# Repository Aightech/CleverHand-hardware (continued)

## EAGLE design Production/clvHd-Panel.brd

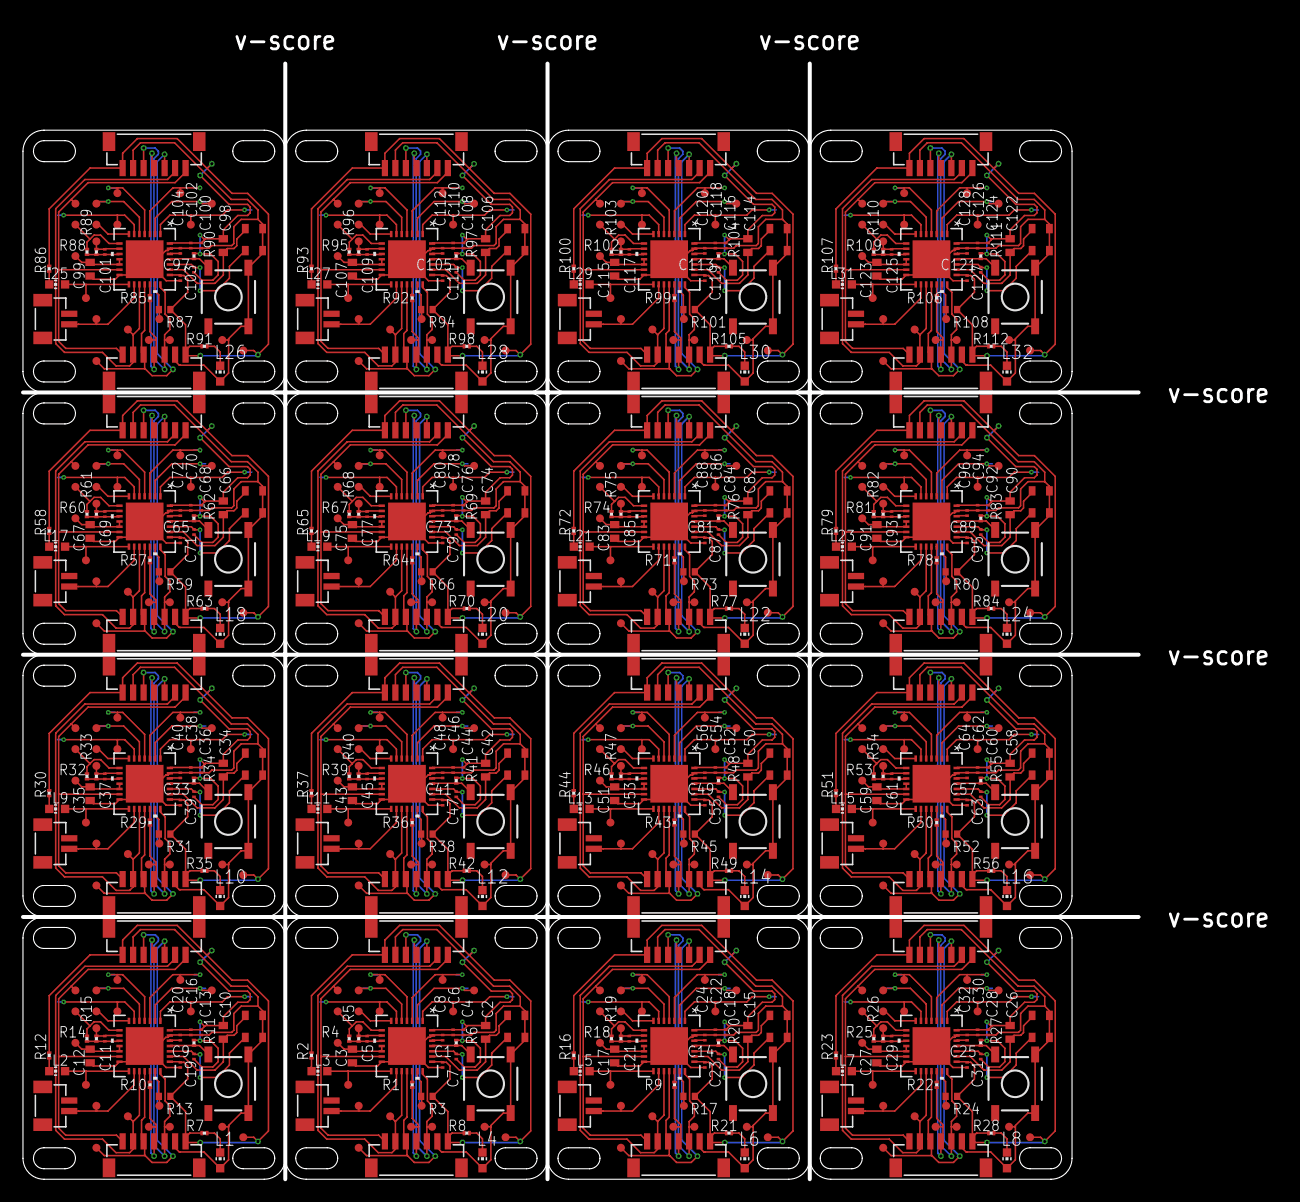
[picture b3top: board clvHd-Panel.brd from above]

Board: 2 copper layers, 106.3 x 106.3 mm, 688 parts (0 on the bottom side), 448 nets.

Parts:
C1, C9, C14, C25, C33, C41, C49, C57, C65, C73, C81, C89, C97, C105, C113, C121: 22pF; C0201
C2, C10, C15, C26, C34, C42, C50, C58, C66, C74, C82, C90, C98, C106, C114, C122: 22pF; C0402
C3, C12, C17, C27, C35, C43, C51, C59, C67, C75, C83, C91, C99, C107, C115, C123: 100nF; C0402
C4, C6, C7, C13, C16, C18, C19, C22, C23, C28, C30, C31, C36, C38, C39, C44, C46, C47, C52, C54, C55, C60, C62, C63, C68, C70, C71, C76, C78, C79, C84, C86, C87, C92, C94, C95, C100, C102, C103, C108, C110, C111, C116, C118, C119, C124, C126, C127: 100nF; C0201
C5, C11, C21, C29, C37, C45, C53, C61, C69, C77, C85, C93, C101, C109, C117, C125: 1nF; C0201
C8, C20, C24, C32, C40, C48, C56, C64, C72, C80, C88, C96, C104, C112, C120, C128: 1000nF; C0201
L1, L2, L3, L4, L5, L6, L7, L8, L9, L10, L11, L12, L13, L14, L15, L16, L17, L18, L19, L20, L21, L22, L23, L24, L25, L26, L27, L28, L29, L30, L31, L32: CHIP-LED0603
R1, R9, R10, R22, R29, R36, R43, R50, R57, R64, R71, R78, R85, R92, R99, R106: 51; R0201
R2, R7, R8, R12, R16, R21, R23, R28, R30, R35, R37, R42, R44, R49, R51, R56, R58, R63, R65, R70, R72, R77, R79, R84, R86, R91, R93, R98, R100, R105, R107, R112: 400; R0201
R3, R13, R17, R24, R31, R38, R45, R52, R59, R66, R73, R80, R87, R94, R101, R108: 1M; R0402
R4, R14, R18, R25, R32, R39, R46, R53, R60, R67, R74, R81, R88, R95, R102, R109: 10k; R0201
R5, R15, R19, R26, R33, R40, R47, R54, R61, R68, R75, R82, R89, R96, R103, R110: 10M; R0201
R6, R11, R20, R27, R34, R41, R48, R55, R62, R69, R76, R83, R90, R97, R104, R111: 1M; R0201
S1, S2, S3, S4, S5, S6, S7, S8, S9, S10, S11, S12, S13, S14, S15, S16: TAC_SWITCHSMD; TACTILE-SWITCH-SMD
TP1, TP2, TP3, TP4, TP5, TP6, TP7, TP8, TP9, TP10, TP11, TP12, TP13, TP14, TP15, TP16, TP17, TP18, TP19, TP20, TP21, TP22, TP23, TP24, TP25, TP26, TP27, TP28, TP29, TP30, TP31, TP32, TP33, TP34, TP35, TP36, TP37, TP38, TP39, TP40, TP41, TP42, TP43, TP44, TP45, TP46, TP47, TP48, TP49, TP50, TP51, TP52, TP53, TP54, TP55, TP56, TP57, TP58, TP59, TP60, TP61, TP62, TP63, TP64, TP65, TP66, TP67, TP68, TP69, TP70, TP71, TP72, TP73, TP74, TP75, TP76, TP77, TP78, TP79, TP80, TP81, TP82, TP83, TP84, TP85, TP86, TP87, TP88, TP89, TP90, TP91, TP92, TP93, TP94, TP95, TP96, TP97, TP98, TP99, TP100, TP101, TP102, TP103, TP104, TP105, TP106, TP107, TP108, TP109, TP110, TP111, TP112, TP113, TP114, TP115, TP116, TP117, TP118, TP119, TP120, TP121, TP122, TP123, TP124, TP125, TP126, TP127, TP128, TP129, TP130, TP131, TP132, TP133, TP134, TP135, TP136, TP137, TP138, TP139, TP140, TP141, TP142, TP143, TP144, TP145, TP146, TP147, TP148, TP149, TP150, TP151, TP152, TP153, TP154, TP155, TP156, TP157, TP158, TP159, TP160, TP161, TP162, TP163, TP164, TP165, TP166, TP167, TP168, TP169, TP170, TP171, TP172, TP173, TP174, TP175, TP176, TP177, TP178, TP179, TP180, TP181, TP182, TP183, TP184, TP185, TP186, TP187, TP188, TP189, TP190, TP191, TP192, TP193, TP194, TP195, TP196, TP197, TP198, TP199, TP200, TP201, TP202, TP203, TP204, TP205, TP206, TP207, TP208, TP209, TP210, TP211, TP212, TP213, TP214, TP215, TP216, TP217, TP218, TP219, TP220, TP221, TP222, TP223, TP224, TP225, TP226, TP227, TP228, TP229, TP230, TP231, TP232, TP233, TP234, TP235, TP236, TP237, TP238, TP239, TP240, TP241, TP242, TP243, TP244, TP245, TP246, TP247, TP248, TP249, TP250, TP251, TP252, TP253, TP254, TP255, TP256, TP257, TP258, TP259, TP260, TP261, TP262, TP263, TP264, TP265, TP266, TP267, TP268, TP269, TP270, TP271, TP272, TP273, TP274, TP275, TP276, TP277, TP278, TP279, TP280, TP281, TP282, TP283, TP284, TP285, TP286, TP287, TP288, TP289, TP290, TP291, TP292, TP293, TP294, TP295, TP296, TP297, TP298, TP299, TP300, TP301, TP302, TP303, TP304, TP305, TP306, TP307, TP308, TP309, TP310, TP311, TP312, TP313, TP314, TP315, TP316, TP317, TP318, TP319, TP320: TEST-POINT3; PAD.03X.03
U1, U2, U3, U4, U5, U6, U7, U8, U9, U10, U11, U12, U13, U14, U15, U16: ADS1293CISQ/NOPB; RSG28_3P6X3P6_TEX
U$1, U$2, U$3, U$4, U$5, U$6, U$7, U$8, U$9, U$10, U$11, U$12, U$13, U$14, U$15, U$16: ASE
X1, X4, X7, X10, X13, X16, X19, X22, X25, X28, X31, X34, X37, X40, X43, X46: BM02B-SRSS-TB
X2, X3, X5, X6, X8, X9, X11, X12, X14, X15, X17, X18, X20, X21, X23, X24, X26, X27, X29, X30, X32, X33, X35, X36, X38, X39, X41, X42, X44, X45, X47, X48: BM07B-SRSS-TB

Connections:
ALARMB: L2.A, TP2.1, U1.15
ALARMB1: L3.A, TP22.1, U2.15
ALARMB2: L5.A, TP42.1, U3.15
ALARMB3: L7.A, TP62.1, U4.15
ALARMB4: L9.A, TP82.1, U5.15
ALARMB5: L11.A, TP102.1, U6.15
ALARMB6: L13.A, TP122.1, U7.15
ALARMB7: L15.A, TP142.1, U8.15
ALARMB8: L17.A, TP162.1, U9.15
ALARMB9: L19.A, TP182.1, U10.15
ALARMB10: L21.A, TP202.1, U11.15
ALARMB11: L23.A, TP222.1, U12.15
ALARMB12: L25.A, TP242.1, U13.15
ALARMB13: L27.A, TP262.1, U14.15
ALARMB14: L29.A, TP282.1, U15.15
ALARMB15: L31.A, TP302.1, U16.15
CLK: TP9.1, U1.21, X2.3, X3.3
CLK1: TP29.1, U2.21, X5.3, X6.3
CLK2: TP49.1, U3.21, X8.3, X9.3
CLK3: TP69.1, U4.21, X11.3, X12.3
CLK4: TP89.1, U5.21, X14.3, X15.3
CLK5: TP109.1, U6.21, X17.3, X18.3
CLK6: TP129.1, U7.21, X20.3, X21.3
CLK7: TP149.1, U8.21, X23.3, X24.3
CLK8: TP169.1, U9.21, X26.3, X27.3
CLK9: TP189.1, U10.21, X29.3, X30.3
CLK10: TP209.1, U11.21, X32.3, X33.3
CLK11: TP229.1, U12.21, X35.3, X36.3
CLK12: TP249.1, U13.21, X38.3, X39.3
CLK13: TP269.1, U14.21, X41.3, X42.3
CLK14: TP289.1, U15.21, X44.3, X45.3
CLK15: TP309.1, U16.21, X47.3, X48.3
CMOUT: R14.1, TP12.1, U1.8
CMOUT1: R4.1, TP32.1, U2.8
CMOUT2: R18.1, TP52.1, U3.8
CMOUT3: R25.1, TP72.1, U4.8
CMOUT4: R32.1, TP92.1, U5.8
CMOUT5: R39.1, TP112.1, U6.8
CMOUT6: R46.1, TP132.1, U7.8
CMOUT7: R53.1, TP152.1, U8.8
CMOUT8: R60.1, TP172.1, U9.8
CMOUT9: R67.1, TP192.1, U10.8
CMOUT10: R74.1, TP212.1, U11.8
CMOUT11: R81.1, TP232.1, U12.8
CMOUT12: R88.1, TP252.1, U13.8
CMOUT13: R95.1, TP272.1, U14.8
CMOUT14: R102.1, TP292.1, U15.8
CMOUT15: R109.1, TP312.1, U16.8
CS: TP10.1, U1.16, X1.1
CS1: TP30.1, U2.16, X4.1
CS2: TP50.1, U3.16, X7.1
CS3: TP70.1, U4.16, X10.1
CS4: TP90.1, U5.16, X13.1
CS5: TP110.1, U6.16, X16.1
CS6: TP130.1, U7.16, X19.1
CS7: TP150.1, U8.16, X22.1
CS8: TP170.1, U9.16, X25.1
CS9: TP190.1, U10.16, X28.1
CS10: TP210.1, U11.16, X31.1
CS11: TP230.1, U12.16, X34.1
CS12: TP250.1, U13.16, X37.1
CS13: TP270.1, U14.16, X40.1
CS14: TP290.1, U15.16, X43.1
CS15: TP310.1, U16.16, X46.1
DIN: TP7.1, U1.18, X2.5, X3.5
DIN1: TP27.1, U2.18, X5.5, X6.5
DIN2: TP47.1, U3.18, X8.5, X9.5
DIN3: TP67.1, U4.18, X11.5, X12.5
DIN4: TP87.1, U5.18, X14.5, X15.5
DIN5: TP107.1, U6.18, X17.5, X18.5
DIN6: TP127.1, U7.18, X20.5, X21.5
DIN7: TP147.1, U8.18, X23.5, X24.5
DIN8: TP167.1, U9.18, X26.5, X27.5
DIN9: TP187.1, U10.18, X29.5, X30.5
DIN10: TP207.1, U11.18, X32.5, X33.5
DIN11: TP227.1, U12.18, X35.5, X36.5
DIN12: TP247.1, U13.18, X38.5, X39.5
DIN13: TP267.1, U14.18, X41.5, X42.5
DIN14: TP287.1, U15.18, X44.5, X45.5
DIN15: TP307.1, U16.18, X47.5, X48.5
DOUT: R10.2, TP6.1, X2.4, X3.4
DOUT1: R1.2, TP26.1, X5.4, X6.4
DOUT2: R9.2, TP46.1, X8.4, X9.4
DOUT3: R22.2, TP66.1, X11.4, X12.4
DOUT4: R29.2, TP86.1, X14.4, X15.4
DOUT5: R36.2, TP106.1, X17.4, X18.4
DOUT6: R43.2, TP126.1, X20.4, X21.4
DOUT7: R50.2, TP146.1, X23.4, X24.4
DOUT8: R57.2, TP166.1, X26.4, X27.4
DOUT9: R64.2, TP186.1, X29.4, X30.4
DOUT10: R71.2, TP206.1, X32.4, X33.4
DOUT11: R78.2, TP226.1, X35.4, X36.4
DOUT12: R85.2, TP246.1, X38.4, X39.4
DOUT13: R92.2, TP266.1, X41.4, X42.4
DOUT14: R99.2, TP286.1, X44.4, X45.4
DOUT15: R106.2, TP306.1, X47.4, X48.4
DRDYB: R13.1, TP1.1, U1.20
DRDYB1: R3.1, TP21.1, U2.20
DRDYB2: R17.1, TP41.1, U3.20
DRDYB3: R24.1, TP61.1, U4.20
DRDYB4: R31.1, TP81.1, U5.20
DRDYB5: R38.1, TP101.1, U6.20
DRDYB6: R45.1, TP121.1, U7.20
DRDYB7: R52.1, TP141.1, U8.20
DRDYB8: R59.1, TP161.1, U9.20
DRDYB9: R66.1, TP181.1, U10.20
DRDYB10: R73.1, TP201.1, U11.20
DRDYB11: R80.1, TP221.1, U12.20
DRDYB12: R87.1, TP241.1, U13.20
DRDYB13: R94.1, TP261.1, U14.20
DRDYB14: R101.1, TP281.1, U15.20
DRDYB15: R108.1, TP301.1, U16.20
GND: C12.2, C13.2, C16.2, C19.2, C20.2, L1.A, S1.3, S1.4, TP4.1, U1.14, U1.27, U1.29, U$1.1, U$1.2, X2.2, X3.2
GND1: C3.2, C4.2, C6.2, C7.2, C8.2, L4.A, S2.3, S2.4, TP24.1, U2.14, U2.27, U2.29, U$2.1, U$2.2, X5.2, X6.2
GND2: C17.2, C18.2, C22.2, C23.2, C24.2, L6.A, S3.3, S3.4, TP44.1, U3.14, U3.27, U3.29, U$3.1, U$3.2, X8.2, X9.2
GND3: C27.2, C28.2, C30.2, C31.2, C32.2, L8.A, S4.3, S4.4, TP64.1, U4.14, U4.27, U4.29, U$4.1, U$4.2, X11.2, X12.2
GND4: C35.2, C36.2, C38.2, C39.2, C40.2, L10.A, S5.3, S5.4, TP84.1, U5.14, U5.27, U5.29, U$5.1, U$5.2, X14.2, X15.2
GND5: C43.2, C44.2, C46.2, C47.2, C48.2, L12.A, S6.3, S6.4, TP104.1, U6.14, U6.27, U6.29, U$6.1, U$6.2, X17.2, X18.2
GND6: C51.2, C52.2, C54.2, C55.2, C56.2, L14.A, S7.3, S7.4, TP124.1, U7.14, U7.27, U7.29, U$7.1, U$7.2, X20.2, X21.2
GND7: C59.2, C60.2, C62.2, C63.2, C64.2, L16.A, S8.3, S8.4, TP144.1, U8.14, U8.27, U8.29, U$8.1, U$8.2, X23.2, X24.2
GND8: C67.2, C68.2, C70.2, C71.2, C72.2, L18.A, S9.3, S9.4, TP164.1, U9.14, U9.27, U9.29, U$9.1, U$9.2, X26.2, X27.2
GND9: C75.2, C76.2, C78.2, C79.2, C80.2, L20.A, S10.3, S10.4, TP184.1, U10.14, U10.27, U10.29, U$10.1, U$10.2, X29.2, X30.2
GND10: C83.2, C84.2, C86.2, C87.2, C88.2, L22.A, S11.3, S11.4, TP204.1, U11.14, U11.27, U11.29, U$11.1, U$11.2, X32.2, X33.2
GND11: C91.2, C92.2, C94.2, C95.2, C96.2, L24.A, S12.3, S12.4, TP224.1, U12.14, U12.27, U12.29, U$12.1, U$12.2, X35.2, X36.2
GND12: C99.2, C100.2, C102.2, C103.2, C104.2, L26.A, S13.3, S13.4, TP244.1, U13.14, U13.27, U13.29, U$13.1, U$13.2, X38.2, X39.2
GND13: C107.2, C108.2, C110.2, C111.2, C112.2, L28.A, S14.3, S14.4, TP264.1, U14.14, U14.27, U14.29, U$14.1, U$14.2, X41.2, X42.2
GND14: C115.2, C116.2, C118.2, C119.2, C120.2, L30.A, S15.3, S15.4, TP284.1, U15.14, U15.27, U15.29, U$15.1, U$15.2, X44.2, X45.2
GND15: C123.2, C124.2, C126.2, C127.2, C128.2, L32.A, S16.3, S16.4, TP304.1, U16.14, U16.27, U16.29, U$16.1, U$16.2, X47.2, X48.2
IN1: TP18.1, U1.1
IN2: TP35.1, U2.4
IN2.: TP17.1, U1.2
IN2.1: TP37.1, U2.2
IN2.2: TP57.1, U3.2
IN2.3: TP77.1, U4.2
IN2.4: TP97.1, U5.2
IN2.5: TP117.1, U6.2
IN2.6: TP137.1, U7.2
IN2.7: TP157.1, U8.2
IN2.8: TP177.1, U9.2
IN2.9: TP197.1, U10.2
IN2.10: TP217.1, U11.2
IN2.11: TP237.1, U12.2
IN2.12: TP257.1, U13.2
IN2.13: TP277.1, U14.2
IN2.14: TP297.1, U15.2
IN2.15: TP317.1, U16.2
IN3: TP16.1, U1.3
IN4: TP15.1, U1.4
IN5: TP14.1, U1.5
IN6: TP13.1, U1.6
IN7: TP33.1, U2.6
IN8: TP36.1, U2.3
IN9: TP34.1, U2.5
IN10: TP38.1, U2.1
IN11: TP55.1, U3.4
IN12: TP53.1, U3.6
IN13: TP56.1, U3.3
IN14: TP54.1, U3.5
IN15: TP58.1, U3.1
IN16: TP75.1, U4.4
IN17: TP73.1, U4.6
IN18: TP76.1, U4.3
IN19: TP74.1, U4.5
IN20: TP78.1, U4.1
IN21: TP95.1, U5.4
IN22: TP93.1, U5.6
IN23: TP96.1, U5.3
IN24: TP94.1, U5.5
IN25: TP98.1, U5.1
IN26: TP115.1, U6.4
IN27: TP113.1, U6.6
IN28: TP116.1, U6.3
IN29: TP114.1, U6.5
IN30: TP118.1, U6.1
IN31: TP135.1, U7.4
IN32: TP133.1, U7.6
IN33: TP136.1, U7.3
IN34: TP134.1, U7.5
IN35: TP138.1, U7.1
IN36: TP155.1, U8.4
IN37: TP153.1, U8.6
IN38: TP156.1, U8.3
IN39: TP154.1, U8.5
IN40: TP158.1, U8.1
IN41: TP175.1, U9.4
IN42: TP173.1, U9.6
IN43: TP176.1, U9.3
IN44: TP174.1, U9.5
IN45: TP178.1, U9.1
IN46: TP195.1, U10.4
IN47: TP193.1, U10.6
IN48: TP196.1, U10.3
IN49: TP194.1, U10.5
IN50: TP198.1, U10.1
IN51: TP215.1, U11.4
IN52: TP213.1, U11.6
IN53: TP216.1, U11.3
IN54: TP214.1, U11.5
IN55: TP218.1, U11.1
IN56: TP235.1, U12.4
IN57: TP233.1, U12.6
IN58: TP236.1, U12.3
IN59: TP234.1, U12.5
IN60: TP238.1, U12.1
IN61: TP255.1, U13.4
IN62: TP253.1, U13.6
IN63: TP256.1, U13.3
IN64: TP254.1, U13.5
IN65: TP258.1, U13.1
IN66: TP275.1, U14.4
IN67: TP273.1, U14.6
IN68: TP276.1, U14.3
IN69: TP274.1, U14.5
IN70: TP278.1, U14.1
IN71: TP295.1, U15.4
IN72: TP293.1, U15.6
IN73: TP296.1, U15.3
IN74: TP294.1, U15.5
IN75: TP298.1, U15.1
IN76: TP315.1, U16.4
IN77: TP313.1, U16.6
IN78: TP316.1, U16.3
IN79: TP314.1, U16.5
IN80: TP318.1, U16.1
unnamed: R11.1, S1.2, U1.25
unnamed: L1.C, R7.2
unnamed: R10.1, U1.19
unnamed: C10.2, U1.23, U$1.3
unnamed: R1.1, U2.19
unnamed: C9.2, U1.24, U$1.4
unnamed: C20.1, U1.26
unnamed: C2.2, U2.23, U$2.3
unnamed: C1.2, U2.24, U$2.4
unnamed: C5.1, R4.2, R5.2, U2.10
unnamed: L2.C, R12.1
unnamed: L3.C, R2.1
unnamed: C11.1, R14.2, R15.2, U1.10
unnamed: C8.1, U2.26
unnamed: R6.1, S2.2, U2.25
unnamed: L4.C, R8.2
unnamed: R9.1, U3.19
unnamed: C15.2, U3.23, U$3.3
unnamed: C14.2, U3.24, U$3.4
unnamed: C21.1, R18.2, R19.2, U3.10
unnamed: L5.C, R16.1
unnamed: C24.1, U3.26
unnamed: R20.1, S3.2, U3.25
unnamed: L6.C, R21.2
unnamed: R22.1, U4.19
unnamed: C26.2, U4.23, U$4.3
unnamed: C25.2, U4.24, U$4.4
unnamed: C29.1, R25.2, R26.2, U4.10
unnamed: L7.C, R23.1
unnamed: C32.1, U4.26
unnamed: R27.1, S4.2, U4.25
unnamed: L8.C, R28.2
unnamed: R29.1, U5.19
unnamed: C34.2, U5.23, U$5.3
unnamed: C33.2, U5.24, U$5.4
unnamed: C37.1, R32.2, R33.2, U5.10
unnamed: L9.C, R30.1
unnamed: C40.1, U5.26
unnamed: R34.1, S5.2, U5.25
unnamed: L10.C, R35.2
unnamed: R36.1, U6.19
unnamed: C42.2, U6.23, U$6.3
unnamed: C41.2, U6.24, U$6.4
unnamed: C45.1, R39.2, R40.2, U6.10
unnamed: L11.C, R37.1
unnamed: C48.1, U6.26
unnamed: R41.1, S6.2, U6.25
unnamed: L12.C, R42.2
unnamed: R43.1, U7.19
unnamed: C50.2, U7.23, U$7.3
unnamed: C49.2, U7.24, U$7.4
unnamed: C53.1, R46.2, R47.2, U7.10
unnamed: L13.C, R44.1
unnamed: C56.1, U7.26
unnamed: R48.1, S7.2, U7.25
unnamed: L14.C, R49.2
unnamed: R50.1, U8.19
unnamed: C58.2, U8.23, U$8.3
unnamed: C57.2, U8.24, U$8.4
unnamed: C61.1, R53.2, R54.2, U8.10
unnamed: L15.C, R51.1
unnamed: C64.1, U8.26
unnamed: R55.1, S8.2, U8.25
unnamed: L16.C, R56.2
unnamed: R57.1, U9.19
unnamed: C66.2, U9.23, U$9.3
unnamed: C65.2, U9.24, U$9.4
unnamed: C69.1, R60.2, R61.2, U9.10
unnamed: L17.C, R58.1
unnamed: C72.1, U9.26
unnamed: R62.1, S9.2, U9.25
unnamed: L18.C, R63.2
unnamed: R64.1, U10.19
unnamed: C74.2, U10.23, U$10.3
unnamed: C73.2, U10.24, U$10.4
unnamed: C77.1, R67.2, R68.2, U10.10
unnamed: L19.C, R65.1
unnamed: C80.1, U10.26
unnamed: R69.1, S10.2, U10.25
unnamed: L20.C, R70.2
unnamed: R71.1, U11.19
unnamed: C82.2, U11.23, U$11.3
unnamed: C81.2, U11.24, U$11.4
unnamed: C85.1, R74.2, R75.2, U11.10
unnamed: L21.C, R72.1
unnamed: C88.1, U11.26
unnamed: R76.1, S11.2, U11.25
unnamed: L22.C, R77.2
unnamed: R78.1, U12.19
unnamed: C90.2, U12.23, U$12.3
unnamed: C89.2, U12.24, U$12.4
unnamed: C93.1, R81.2, R82.2, U12.10
unnamed: L23.C, R79.1
unnamed: C96.1, U12.26
unnamed: R83.1, S12.2, U12.25
unnamed: L24.C, R84.2
unnamed: R85.1, U13.19
unnamed: C98.2, U13.23, U$13.3
unnamed: C97.2, U13.24, U$13.4
unnamed: C101.1, R88.2, R89.2, U13.10
unnamed: L25.C, R86.1
unnamed: C104.1, U13.26
unnamed: R90.1, S13.2, U13.25
unnamed: L26.C, R91.2
unnamed: R92.1, U14.19
unnamed: C106.2, U14.23, U$14.3
unnamed: C105.2, U14.24, U$14.4
unnamed: C109.1, R95.2, R96.2, U14.10
unnamed: L27.C, R93.1
unnamed: C112.1, U14.26
unnamed: R97.1, S14.2, U14.25
unnamed: L28.C, R98.2
unnamed: R99.1, U15.19
unnamed: C114.2, U15.23, U$15.3
unnamed: C113.2, U15.24, U$15.4
unnamed: C117.1, R102.2, R103.2, U15.10
unnamed: L29.C, R100.1
unnamed: C120.1, U15.26
unnamed: R104.1, S15.2, U15.25
unnamed: L30.C, R105.2
unnamed: R106.1, U16.19
unnamed: C122.2, U16.23, U$16.3
unnamed: C121.2, U16.24, U$16.4
unnamed: C125.1, R109.2, R110.2, U16.10
unnamed: L31.C, R107.1
unnamed: C128.1, U16.26
unnamed: R111.1, S16.2, U16.25
unnamed: L32.C, R112.2
RLDOUT: C11.2, R15.1, TP19.1, U1.9
RLDOUT1: C5.2, R5.1, TP39.1, U2.9
RLDOUT2: C21.2, R19.1, TP59.1, U3.9
RLDOUT3: C29.2, R26.1, TP79.1, U4.9
RLDOUT4: C37.2, R33.1, TP99.1, U5.9
RLDOUT5: C45.2, R40.1, TP119.1, U6.9
RLDOUT6: C53.2, R47.1, TP139.1, U7.9
RLDOUT7: C61.2, R54.1, TP159.1, U8.9
RLDOUT8: C69.2, R61.1, TP179.1, U9.9
RLDOUT9: C77.2, R68.1, TP199.1, U10.9
RLDOUT10: C85.2, R75.1, TP219.1, U11.9
RLDOUT11: C93.2, R82.1, TP239.1, U12.9
RLDOUT12: C101.2, R89.1, TP259.1, U13.9
RLDOUT13: C109.2, R96.1, TP279.1, U14.9
RLDOUT14: C117.2, R103.1, TP299.1, U15.9
RLDOUT15: C125.2, R110.1, TP319.1, U16.9
RLDREF: C12.1, TP20.1, U1.11, U1.12
RLDREF1: C3.1, TP40.1, U2.11, U2.12
RLDREF2: C17.1, TP60.1, U3.11, U3.12
RLDREF3: C27.1, TP80.1, U4.11, U4.12
RLDREF4: C35.1, TP100.1, U5.11, U5.12
RLDREF5: C43.1, TP120.1, U6.11, U6.12
RLDREF6: C51.1, TP140.1, U7.11, U7.12
RLDREF7: C59.1, TP160.1, U8.11, U8.12
RLDREF8: C67.1, TP180.1, U9.11, U9.12
RLDREF9: C75.1, TP200.1, U10.11, U10.12
RLDREF10: C83.1, TP220.1, U11.11, U11.12
RLDREF11: C91.1, TP240.1, U12.11, U12.12
RLDREF12: C99.1, TP260.1, U13.11, U13.12
RLDREF13: C107.1, TP280.1, U14.11, U14.12
RLDREF14: C115.1, TP300.1, U15.11, U15.12
RLDREF15: C123.1, TP320.1, U16.11, U16.12
SCLK: TP5.1, U1.17, X2.6, X3.6
SCLK1: TP25.1, U2.17, X5.6, X6.6
SCLK2: TP45.1, U3.17, X8.6, X9.6
SCLK3: TP65.1, U4.17, X11.6, X12.6
SCLK4: TP85.1, U5.17, X14.6, X15.6
SCLK5: TP105.1, U6.17, X17.6, X18.6
SCLK6: TP125.1, U7.17, X20.6, X21.6
SCLK7: TP145.1, U8.17, X23.6, X24.6
SCLK8: TP165.1, U9.17, X26.6, X27.6
SCLK9: TP185.1, U10.17, X29.6, X30.6
SCLK10: TP205.1, U11.17, X32.6, X33.6
SCLK11: TP225.1, U12.17, X35.6, X36.6
SCLK12: TP245.1, U13.17, X38.6, X39.6
SCLK13: TP265.1, U14.17, X41.6, X42.6
SCLK14: TP285.1, U15.17, X44.6, X45.6
SCLK15: TP305.1, U16.17, X47.6, X48.6
SYNCB: TP8.1, U1.13, X2.7, X3.7
SYNCB1: TP28.1, U2.13, X5.7, X6.7
SYNCB2: TP48.1, U3.13, X8.7, X9.7
SYNCB3: TP68.1, U4.13, X11.7, X12.7
SYNCB4: TP88.1, U5.13, X14.7, X15.7
SYNCB5: TP108.1, U6.13, X17.7, X18.7
SYNCB6: TP128.1, U7.13, X20.7, X21.7
SYNCB7: TP148.1, U8.13, X23.7, X24.7
SYNCB8: TP168.1, U9.13, X26.7, X27.7
SYNCB9: TP188.1, U10.13, X29.7, X30.7
SYNCB10: TP208.1, U11.13, X32.7, X33.7
SYNCB11: TP228.1, U12.13, X35.7, X36.7
SYNCB12: TP248.1, U13.13, X38.7, X39.7
SYNCB13: TP268.1, U14.13, X41.7, X42.7
SYNCB14: TP288.1, U15.13, X44.7, X45.7
SYNCB15: TP308.1, U16.13, X47.7, X48.7
VDD: C9.1, C10.1, C13.1, C16.1, C19.1, R7.1, R11.2, R12.2, R13.2, TP3.1, U1.22, U1.28, X2.1, X3.1
VDD1: C1.1, C2.1, C4.1, C6.1, C7.1, R2.2, R3.2, R6.2, R8.1, TP23.1, U2.22, U2.28, X5.1, X6.1
VDD2: C14.1, C15.1, C18.1, C22.1, C23.1, R16.2, R17.2, R20.2, R21.1, TP43.1, U3.22, U3.28, X8.1, X9.1
VDD3: C25.1, C26.1, C28.1, C30.1, C31.1, R23.2, R24.2, R27.2, R28.1, TP63.1, U4.22, U4.28, X11.1, X12.1
VDD4: C33.1, C34.1, C36.1, C38.1, C39.1, R30.2, R31.2, R34.2, R35.1, TP83.1, U5.22, U5.28, X14.1, X15.1
VDD5: C41.1, C42.1, C44.1, C46.1, C47.1, R37.2, R38.2, R41.2, R42.1, TP103.1, U6.22, U6.28, X17.1, X18.1
VDD6: C49.1, C50.1, C52.1, C54.1, C55.1, R44.2, R45.2, R48.2, R49.1, TP123.1, U7.22, U7.28, X20.1, X21.1
VDD7: C57.1, C58.1, C60.1, C62.1, C63.1, R51.2, R52.2, R55.2, R56.1, TP143.1, U8.22, U8.28, X23.1, X24.1
VDD8: C65.1, C66.1, C68.1, C70.1, C71.1, R58.2, R59.2, R62.2, R63.1, TP163.1, U9.22, U9.28, X26.1, X27.1
VDD9: C73.1, C74.1, C76.1, C78.1, C79.1, R65.2, R66.2, R69.2, R70.1, TP183.1, U10.22, U10.28, X29.1, X30.1
VDD10: C81.1, C82.1, C84.1, C86.1, C87.1, R72.2, R73.2, R76.2, R77.1, TP203.1, U11.22, U11.28, X32.1, X33.1
VDD11: C89.1, C90.1, C92.1, C94.1, C95.1, R79.2, R80.2, R83.2, R84.1, TP223.1, U12.22, U12.28, X35.1, X36.1
VDD12: C97.1, C98.1, C100.1, C102.1, C103.1, R86.2, R87.2, R90.2, R91.1, TP243.1, U13.22, U13.28, X38.1, X39.1
VDD13: C105.1, C106.1, C108.1, C110.1, C111.1, R93.2, R94.2, R97.2, R98.1, TP263.1, U14.22, U14.28, X41.1, X42.1
VDD14: C113.1, C114.1, C116.1, C118.1, C119.1, R100.2, R101.2, R104.2, R105.1, TP283.1, U15.22, U15.28, X44.1, X45.1
VDD15: C121.1, C122.1, C124.1, C126.1, C127.1, R107.2, R108.2, R111.2, R112.1, TP303.1, U16.22, U16.28, X47.1, X48.1
WCT: TP11.1, U1.7
WCT1: TP31.1, U2.7
WCT2: TP51.1, U3.7
WCT3: TP71.1, U4.7
WCT4: TP91.1, U5.7
WCT5: TP111.1, U6.7
WCT6: TP131.1, U7.7
WCT7: TP151.1, U8.7
WCT8: TP171.1, U9.7
WCT9: TP191.1, U10.7
WCT10: TP211.1, U11.7
WCT11: TP231.1, U12.7
WCT12: TP251.1, U13.7
WCT13: TP271.1, U14.7
WCT14: TP291.1, U15.7
WCT15: TP311.1, U16.7
